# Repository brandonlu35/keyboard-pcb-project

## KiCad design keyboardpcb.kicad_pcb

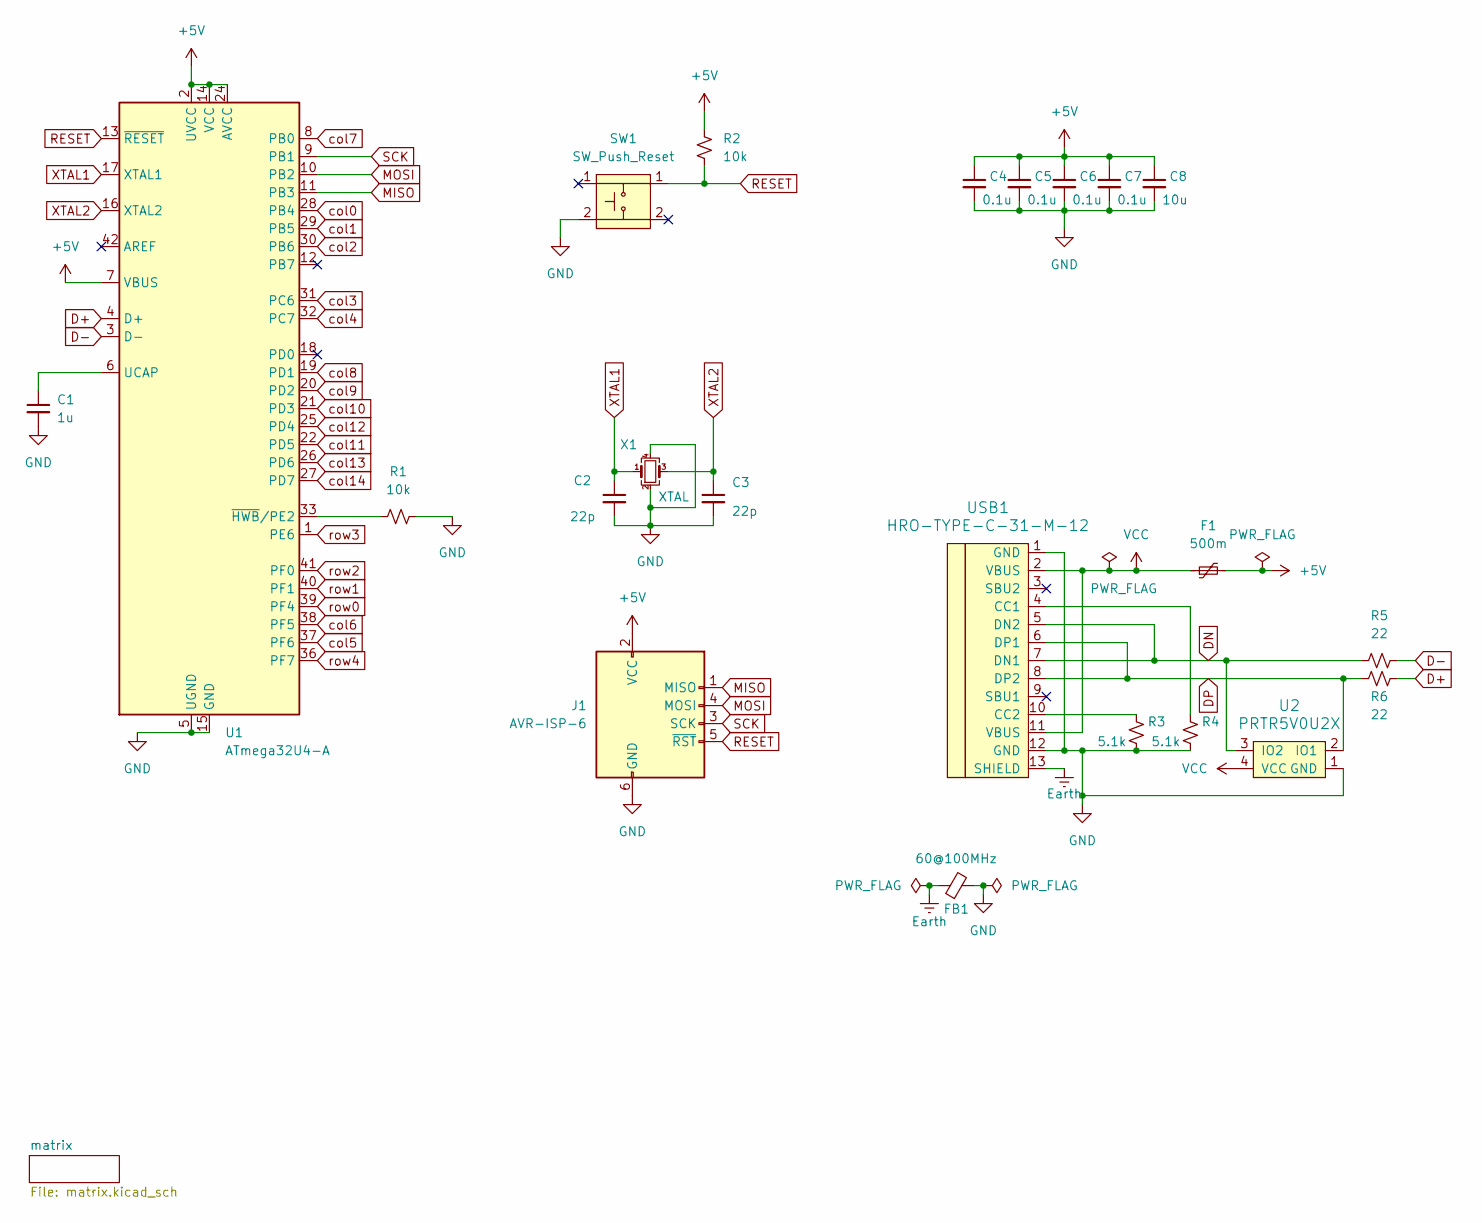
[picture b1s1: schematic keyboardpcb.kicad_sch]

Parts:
C1: 1u; C_0805_2012Metric_Pad1.18x1.45mm_HandSolder
C2, C3: 22p; C_0805_2012Metric_Pad1.18x1.45mm_HandSolder
C4, C5, C6, C7: 0.1u; C_0805_2012Metric_Pad1.18x1.45mm_HandSolder
C8: 10u; C_0805_2012Metric_Pad1.18x1.45mm_HandSolder
F1: 500m; Fuse_1206_3216Metric_Pad1.42x1.75mm_HandSolder
FB1: 60@100MHz; L_0805_2012Metric_Pad1.15x1.40mm_HandSolder
J1: AVR-ISP-6; Reset_Pretty-Mask
R1, R2: 10k; R_0805_2012Metric_Pad1.20x1.40mm_HandSolder
R3, R4: 5.1k; R_0805_2012Metric_Pad1.20x1.40mm_HandSolder
R5, R6: 22; R_0805_2012Metric_Pad1.20x1.40mm_HandSolder
SW1: SW_Push_Reset; SW_SPST_SKQG_WithStem
U1: ATmega32U4-A; TQFP-44_10x10mm_P0.8mm
U2: PRTR5V0U2X; SOT143B
USB1: HRO-TYPE-C-31-M-12; HRO-TYPE-C-31-M-12-HandSoldering
X1: XTAL; Crystal_SMD_3225-4Pin_3.2x2.5mm_HandSoldering

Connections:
+5V: C4.1, C5.1, C6.1, C7.1, C8.1, F1.2, J1.2 (VCC), R2.1, U1.2 (UVCC), U1.7 (VBUS), U1.14 (VCC), U1.24 (AVCC), U1.34 (VCC), U1.44 (AVCC)
D+: R6.2, U1.4 (D+)
D-: R5.2, U1.3 (D-)
DN: R5.1, U2.3 (IO2), USB1.5 (DN2), USB1.7 (DN1)
DP: R6.1, U2.2 (IO1), USB1.6 (DP1), USB1.8 (DP2)
Earth: FB1.1, USB1.13 (SHIELD)
GND: C1.2, C2.2, C3.2, C4.2, C5.2, C6.2, C7.2, C8.2, FB1.2, J1.6 (GND), R1.2, R3.2, R4.2, SW1.2, U1.5 (UGND), U1.15 (GND), U1.23 (GND), U1.35 (GND), U1.43 (GND), U2.1 (GND), USB1.1 (GND), USB1.12 (GND), X1.2, X1.4
MISO: J1.1 (MISO), U1.11 (PB3)
MOSI: J1.4 (MOSI), U1.10 (PB2)
unnamed: C1.1, U1.6 (UCAP)
unnamed: R1.1, U1.33 (~HWB/PE2)
unnamed: R4.1, USB1.4 (CC1)
unnamed: R3.1, USB1.10 (CC2)
RESET: J1.5 (~RST), R2.2, SW1.1, U1.13 (~RESET)
SCK: J1.3 (SCK), U1.9 (PB1)
VCC: F1.1, U2.4 (VCC), USB1.2 (VBUS), USB1.11 (VBUS)
XTAL1: C2.1, U1.17 (XTAL1), X1.1
XTAL2: C3.1, U1.16 (XTAL2), X1.3
col0: U1.28 (PB4); also elsewhere on the board
col1: U1.29 (PB5); also elsewhere on the board
col2: U1.30 (PB6); also elsewhere on the board
col3: U1.31 (PC6); also elsewhere on the board
col4: U1.32 (PC7); also elsewhere on the board
col5: U1.37 (PF6); also elsewhere on the board
col6: U1.38 (PF5); also elsewhere on the board
col7: U1.8 (PB0); also elsewhere on the board
col8: U1.19 (PD1); also elsewhere on the board
col9: U1.20 (PD2); also elsewhere on the board
col10: U1.21 (PD3); also elsewhere on the board
col11: U1.22 (PD5); also elsewhere on the board
col12: U1.25 (PD4); also elsewhere on the board
col13: U1.26 (PD6); also elsewhere on the board
col14: U1.27 (PD7); also elsewhere on the board
row0: U1.39 (PF4); also elsewhere on the board
row1: U1.40 (PF1); also elsewhere on the board
row2: U1.41 (PF0); also elsewhere on the board
row3: U1.1 (PE6); also elsewhere on the board
row4: U1.36 (PF7); also elsewhere on the board

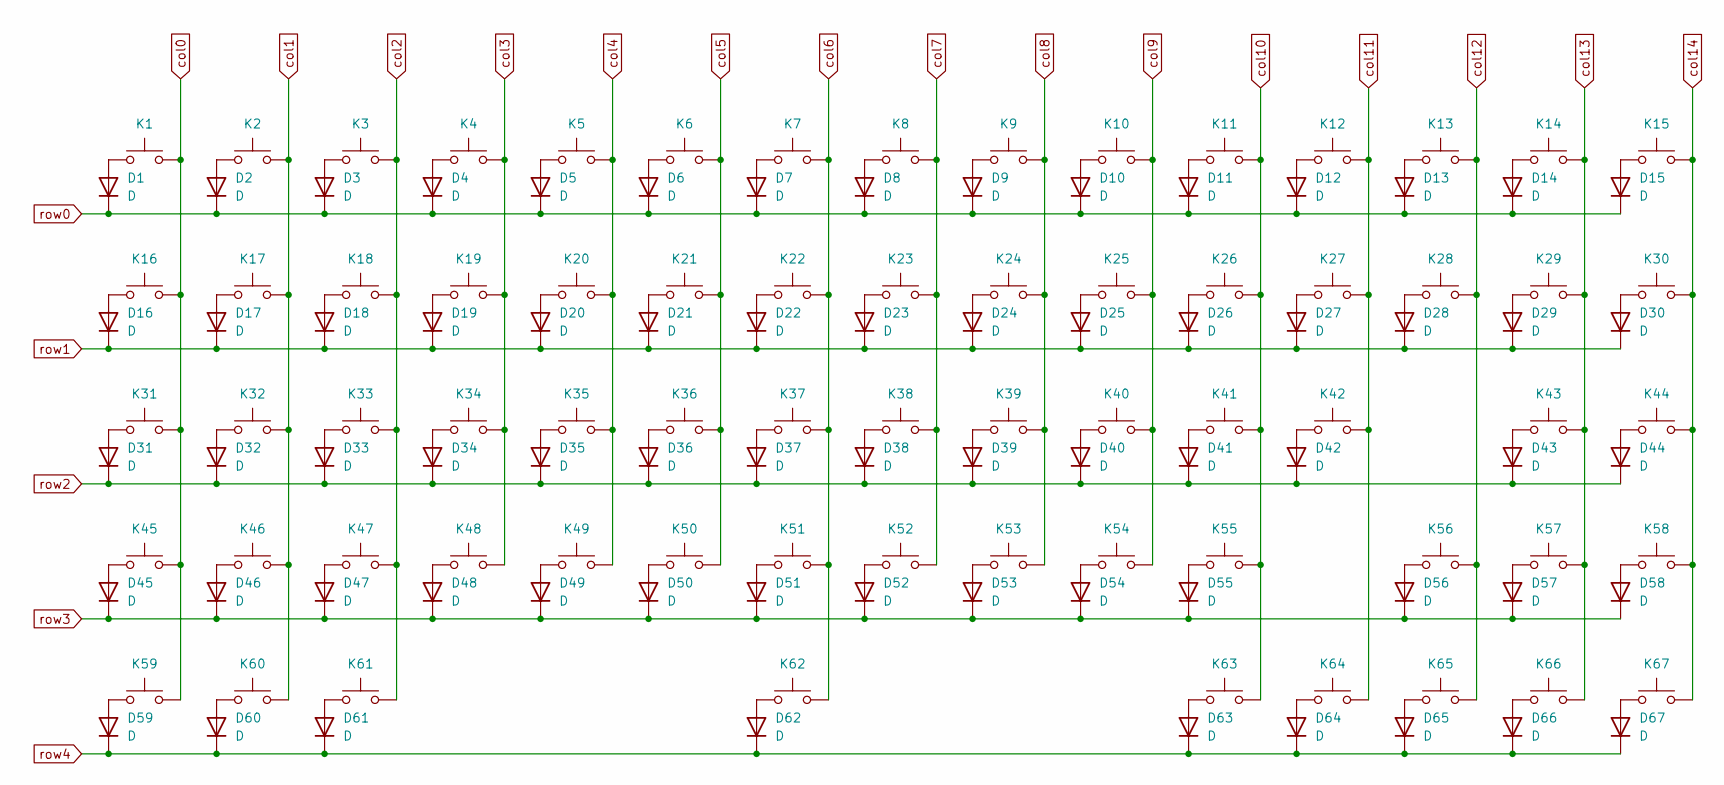
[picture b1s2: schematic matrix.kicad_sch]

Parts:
D1, D2, D3, D4, D5, D6, D7, D8, D9, D10, D11, D12, D13, D14, D15, D16, D17, D18, D19, D20, D21, D22, D23, D24, D25, D26, D27, D28, D29, D30, D31, D32, D33, D34, D35, D36, D37, D38, D39, D40, D41, D42, D43, D44, D45, D46, D47, D48, D49, D50, D51, D52, D53, D54, D55, D56, D57, D58, D59, D60, D61, D62, D63, D64, D65, D66, D67: D; D_SOD-123
K1: ESC; MX-Solderable-1U
K2: 1; MX-Solderable-1U
K3: 2; MX-Solderable-1U
K4: 3; MX-Solderable-1U
K5: 4; MX-Solderable-1U
K6: 5; MX-Solderable-1U
K7: 6; MX-Solderable-1U
K8: 7; MX-Solderable-1U
K9: 8; MX-Solderable-1U
K10: 9; MX-Solderable-1U
K11: 0; MX-Solderable-1U
K12: -_; MX-Solderable-1U
K13: =+; MX-Solderable-1U
K14: BSPC; MX-Solderable-2U
K15: PGUP; MX-Solderable-1U
K16: TAB; MX-Solderable-1.5U
K17: Q; MX-Solderable-1U
K18: W; MX-Solderable-1U
K19: E; MX-Solderable-1U
K20: R; MX-Solderable-1U
K21: T; MX-Solderable-1U
K22: Y; MX-Solderable-1U
K23: U; MX-Solderable-1U
K24: I; MX-Solderable-1U
K25: O; MX-Solderable-1U
K26: P; MX-Solderable-1U
K27: [{; MX-Solderable-1U
K28: ]}; MX-Solderable-1U
K29: \|; MX-Solderable-1.5U
K30: PGDN; MX-Solderable-1U
K31: CAPS; MX-Solderable-1.75U
K32: A; MX-Solderable-1U
K33: S; MX-Solderable-1U
K34: D; MX-Solderable-1U
K35: F; MX-Solderable-1U
K36: G; MX-Solderable-1U
K37: H; MX-Solderable-1U
K38: J; MX-Solderable-1U
K39: K; MX-Solderable-1U
K40: L; MX-Solderable-1U
K41: ; :; MX-Solderable-1U
K42: ' "; MX-Solderable-1U
K43: ENT; MX-Solderable-2.25U
K44: INS; MX-Solderable-1U
K45: LSHFT; MX-Solderable-2.25U
K46: Z; MX-Solderable-1U
K47: X; MX-Solderable-1U
K48: C; MX-Solderable-1U
K49: V; MX-Solderable-1U
K50: B; MX-Solderable-1U
K51: N; MX-Solderable-1U
K52: M; MX-Solderable-1U
K53: ,<; MX-Solderable-1U
K54: .>; MX-Solderable-1U
K55: /?; MX-Solderable-1U
K56: RSHFT; MX-Solderable-1.75U
K57: UP; MX-Solderable-1U
K58: DEL; MX-Solderable-1U
K59: CTRL; MX-Solderable-1.5U
K60: WIN; MX-Solderable-1.25U
K61: LALT; MX-Solderable-1.5U
K62: SPC; MX-Solderable-6.25U
K63: RALT; MX-Solderable-1.25U
K64: FN; MX-Solderable-1.25U
K65: LEFT; MX-Solderable-1U
K66: DOWN; MX-Solderable-1U
K67: RGHT; MX-Solderable-1U

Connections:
unnamed: D1.2 (A), K1.1
unnamed: D2.2 (A), K2.1
unnamed: D3.2 (A), K3.1
unnamed: D4.2 (A), K4.1
unnamed: D5.2 (A), K5.1
unnamed: D6.2 (A), K6.1
unnamed: D7.2 (A), K7.1
unnamed: D8.2 (A), K8.1
unnamed: D9.2 (A), K9.1
unnamed: D10.2 (A), K10.1
unnamed: D11.2 (A), K11.1
unnamed: D12.2 (A), K12.1
unnamed: D13.2 (A), K13.1
unnamed: D14.2 (A), K14.1
unnamed: D15.2 (A), K15.1
unnamed: D16.2 (A), K16.1
unnamed: D17.2 (A), K17.1
unnamed: D18.2 (A), K18.1
unnamed: D19.2 (A), K19.1
unnamed: D20.2 (A), K20.1
unnamed: D21.2 (A), K21.1
unnamed: D22.2 (A), K22.1
unnamed: D23.2 (A), K23.1
unnamed: D24.2 (A), K24.1
unnamed: D25.2 (A), K25.1
unnamed: D26.2 (A), K26.1
unnamed: D27.2 (A), K27.1
unnamed: D28.2 (A), K28.1
unnamed: D29.2 (A), K29.1
unnamed: D30.2 (A), K30.1
unnamed: D31.2 (A), K31.1
unnamed: D32.2 (A), K32.1
unnamed: D33.2 (A), K33.1
unnamed: D34.2 (A), K34.1
unnamed: D35.2 (A), K35.1
unnamed: D36.2 (A), K36.1
unnamed: D37.2 (A), K37.1
unnamed: D38.2 (A), K38.1
unnamed: D39.2 (A), K39.1
unnamed: D40.2 (A), K40.1
unnamed: D41.2 (A), K41.1
unnamed: D42.2 (A), K42.1
unnamed: D43.2 (A), K43.1
unnamed: D44.2 (A), K44.1
unnamed: D45.2 (A), K45.1
unnamed: D46.2 (A), K46.1
unnamed: D47.2 (A), K47.1
unnamed: D48.2 (A), K48.1
unnamed: D49.2 (A), K49.1
unnamed: D50.2 (A), K50.1
unnamed: D51.2 (A), K51.1
unnamed: D52.2 (A), K52.1
unnamed: D53.2 (A), K53.1
unnamed: D54.2 (A), K54.1
unnamed: D55.2 (A), K55.1
unnamed: D56.2 (A), K56.1
unnamed: D57.2 (A), K57.1
unnamed: D58.2 (A), K58.1
unnamed: D59.2 (A), K59.1
unnamed: D60.2 (A), K60.1
unnamed: D61.2 (A), K61.1
unnamed: D62.2 (A), K62.1
unnamed: D63.2 (A), K63.1
unnamed: D64.2 (A), K64.1
unnamed: D65.2 (A), K65.1
unnamed: D66.2 (A), K66.1
unnamed: D67.2 (A), K67.1
col0: K1.2, K16.2, K31.2, K45.2, K59.2; also elsewhere on the board
col1: K2.2, K17.2, K32.2, K46.2, K60.2; also elsewhere on the board
col2: K3.2, K18.2, K33.2, K47.2, K61.2; also elsewhere on the board
col3: K4.2, K19.2, K34.2, K48.2; also elsewhere on the board
col4: K5.2, K20.2, K35.2, K49.2; also elsewhere on the board
col5: K6.2, K21.2, K36.2, K50.2; also elsewhere on the board
col6: K7.2, K22.2, K37.2, K51.2, K62.2; also elsewhere on the board
col7: K8.2, K23.2, K38.2, K52.2; also elsewhere on the board
col8: K9.2, K24.2, K39.2, K53.2; also elsewhere on the board
col9: K10.2, K25.2, K40.2, K54.2; also elsewhere on the board
col10: K11.2, K26.2, K41.2, K55.2, K63.2; also elsewhere on the board
col11: K12.2, K27.2, K42.2, K64.2; also elsewhere on the board
col12: K13.2, K28.2, K56.2, K65.2; also elsewhere on the board
col13: K14.2, K29.2, K43.2, K57.2, K66.2; also elsewhere on the board
col14: K15.2, K30.2, K44.2, K58.2, K67.2; also elsewhere on the board
row0: D1.1 (K), D2.1 (K), D3.1 (K), D4.1 (K), D5.1 (K), D6.1 (K), D7.1 (K), D8.1 (K), D9.1 (K), D10.1 (K), D11.1 (K), D12.1 (K), D13.1 (K), D14.1 (K), D15.1 (K); also elsewhere on the board
row1: D16.1 (K), D17.1 (K), D18.1 (K), D19.1 (K), D20.1 (K), D21.1 (K), D22.1 (K), D23.1 (K), D24.1 (K), D25.1 (K), D26.1 (K), D27.1 (K), D28.1 (K), D29.1 (K), D30.1 (K); also elsewhere on the board
row2: D31.1 (K), D32.1 (K), D33.1 (K), D34.1 (K), D35.1 (K), D36.1 (K), D37.1 (K), D38.1 (K), D39.1 (K), D40.1 (K), D41.1 (K), D42.1 (K), D43.1 (K), D44.1 (K); also elsewhere on the board
row3: D45.1 (K), D46.1 (K), D47.1 (K), D48.1 (K), D49.1 (K), D50.1 (K), D51.1 (K), D52.1 (K), D53.1 (K), D54.1 (K), D55.1 (K), D56.1 (K), D57.1 (K), D58.1 (K); also elsewhere on the board
row4: D59.1 (K), D60.1 (K), D61.1 (K), D62.1 (K), D63.1 (K), D64.1 (K), D65.1 (K), D66.1 (K), D67.1 (K); also elsewhere on the board

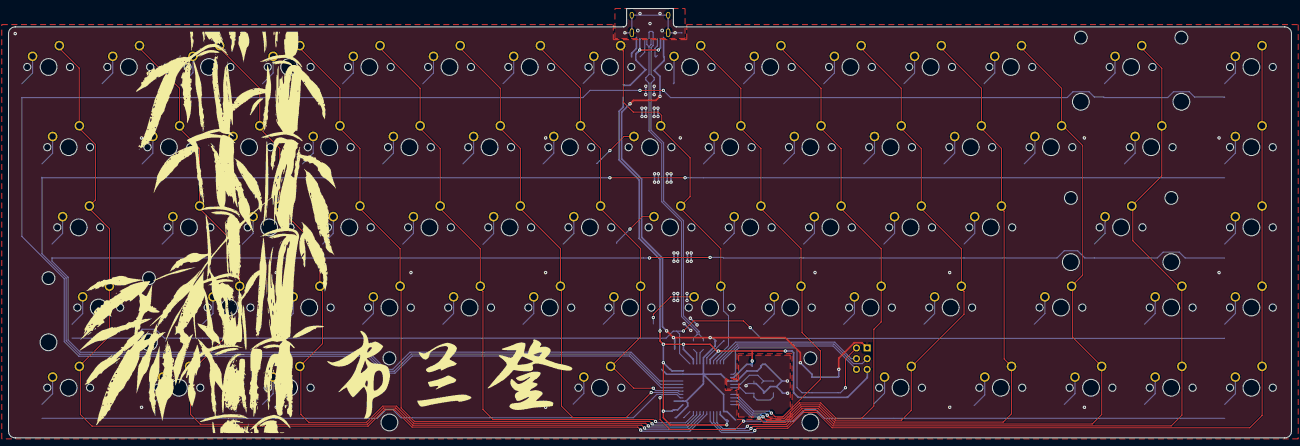
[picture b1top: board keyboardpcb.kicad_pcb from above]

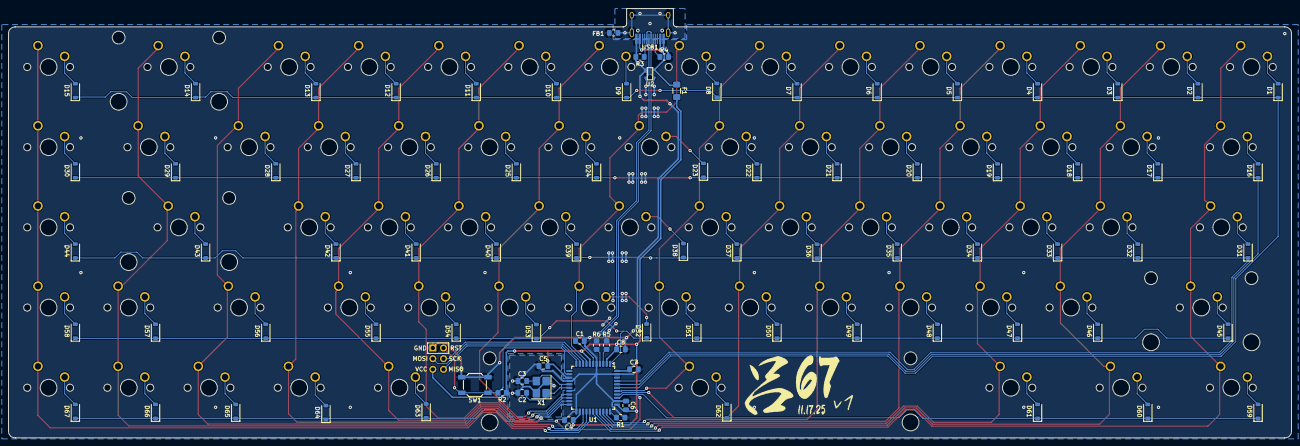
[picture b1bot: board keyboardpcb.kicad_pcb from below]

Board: 2 copper layers, 304.8 x 102.0 mm, 156 parts (89 on the bottom side), 105 nets.

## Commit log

2025-11-09 Add keyboard libraries as git submodules
2025-11-12 Matrix and MCU Schematic
2025-11-15 Matrix and pcb layout
2025-11-20 Final Complete
2025-11-20 PCB Footprint switched to MX only, layout changed
